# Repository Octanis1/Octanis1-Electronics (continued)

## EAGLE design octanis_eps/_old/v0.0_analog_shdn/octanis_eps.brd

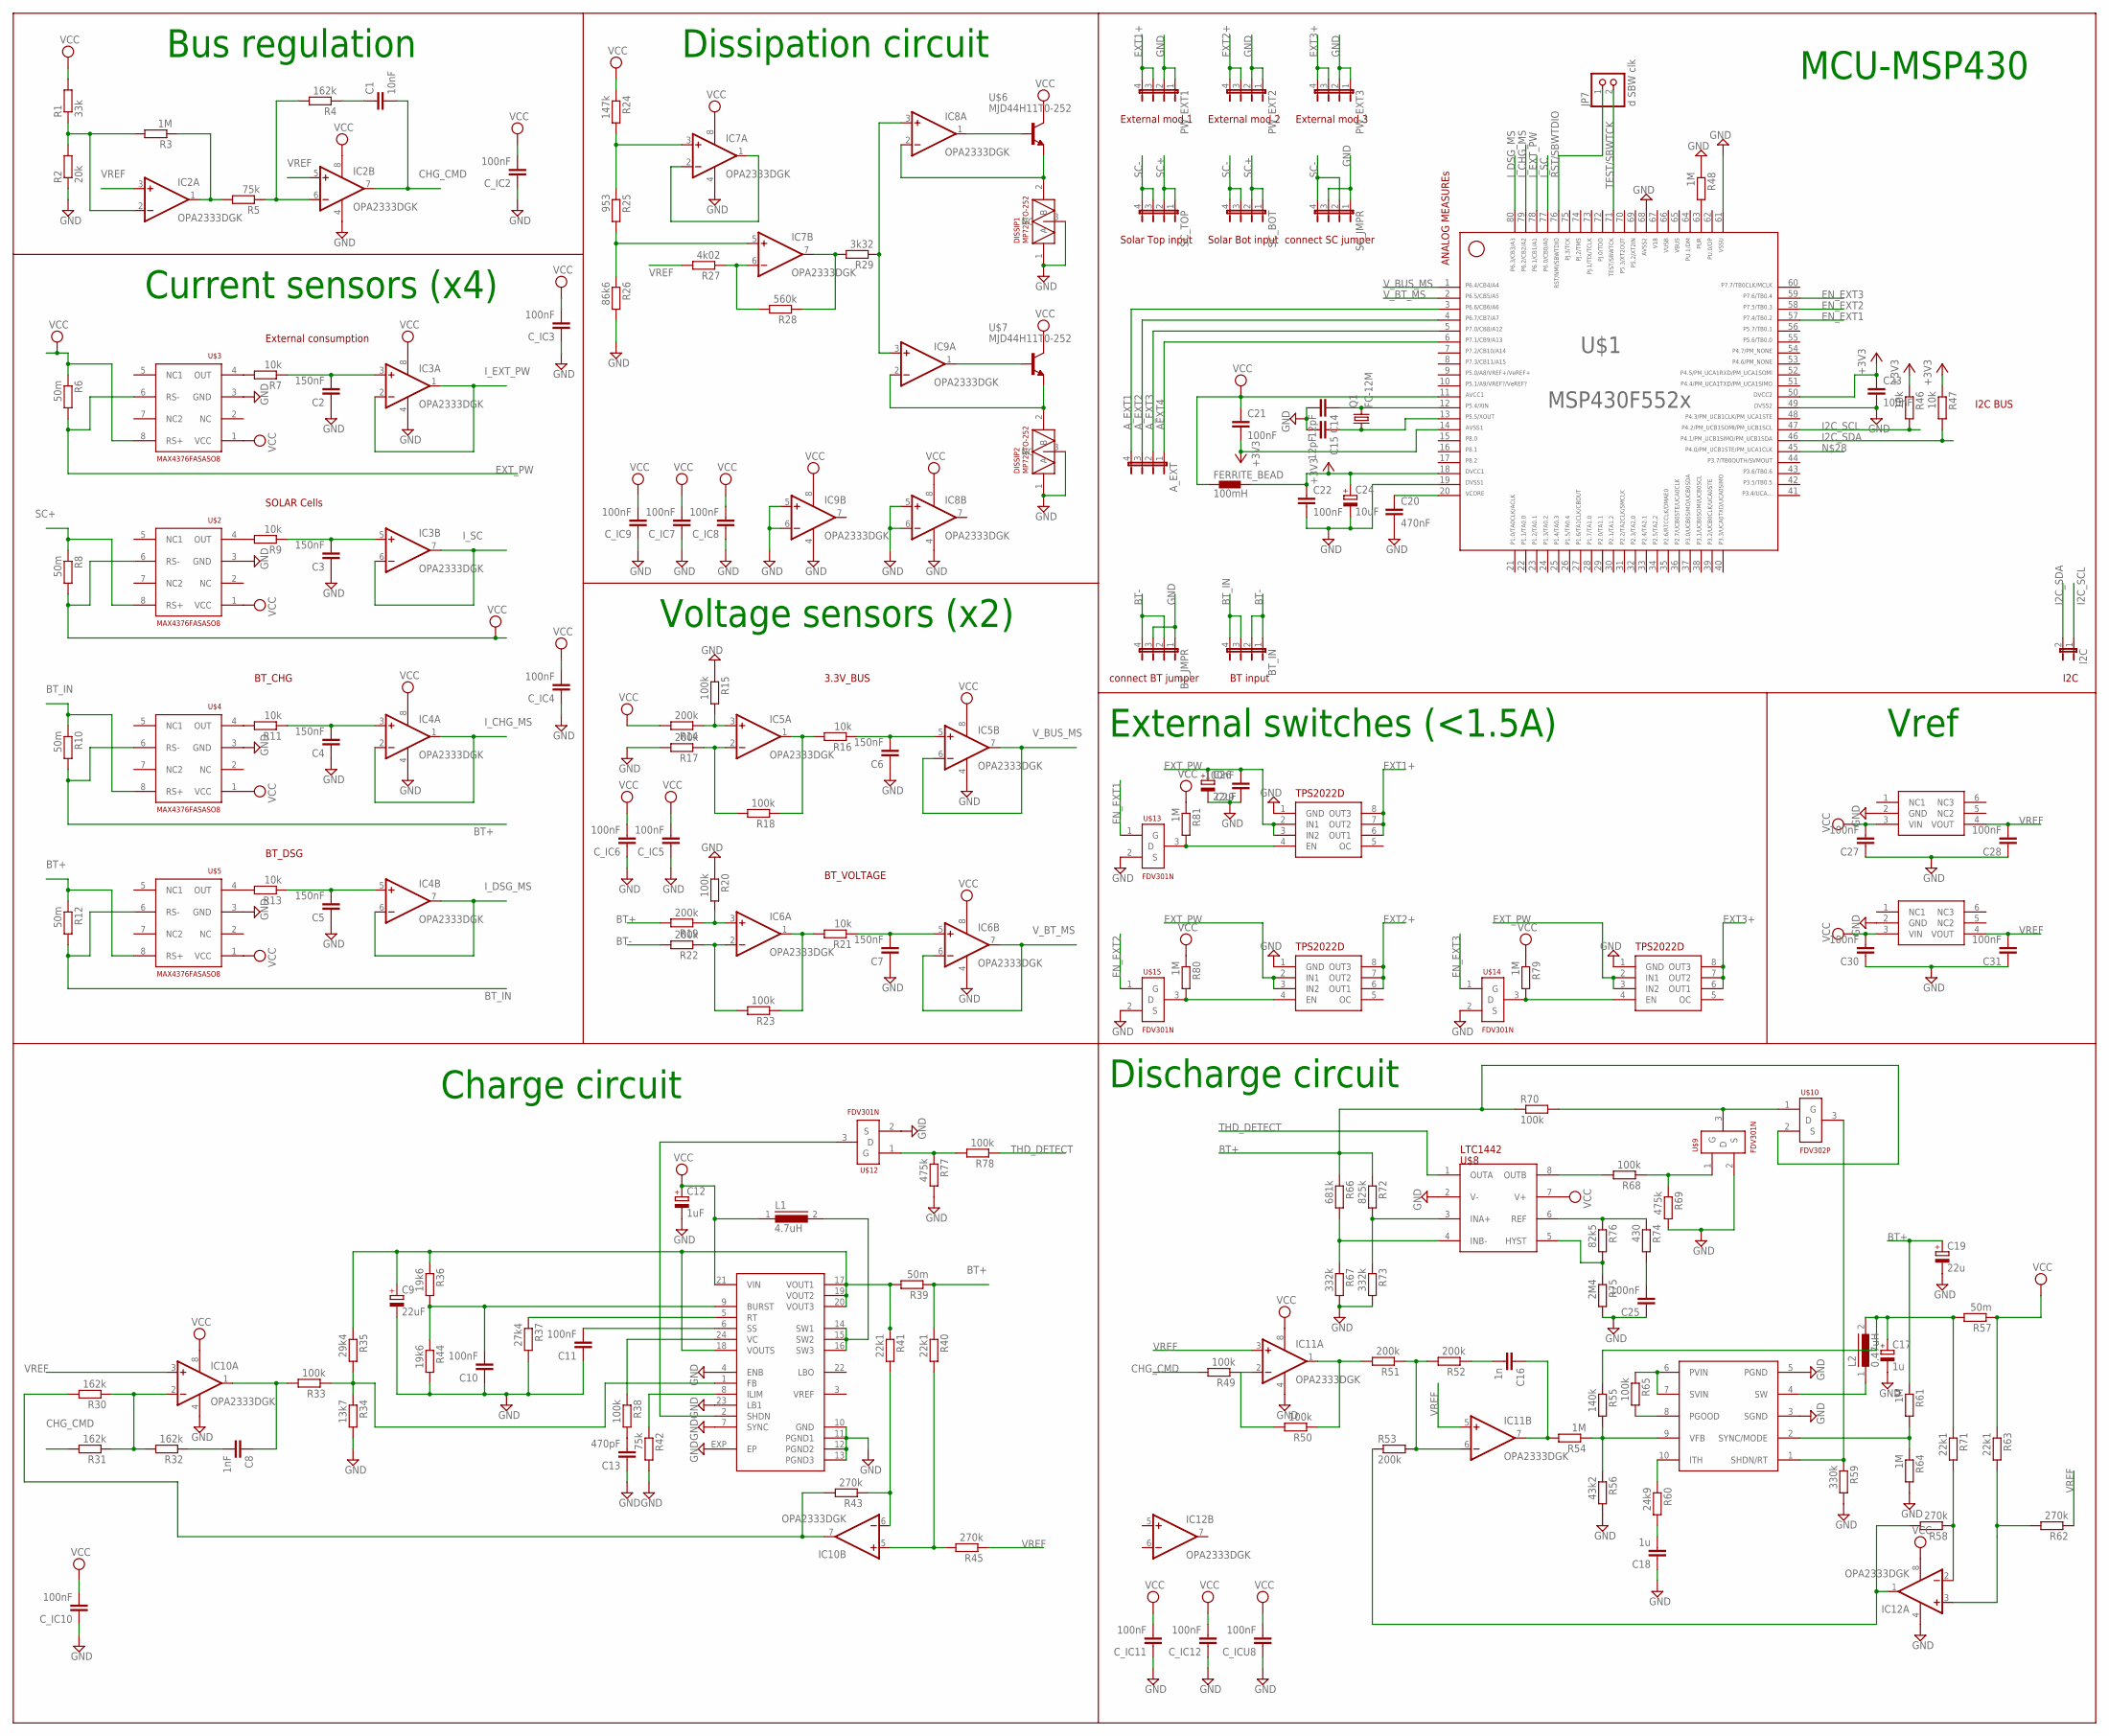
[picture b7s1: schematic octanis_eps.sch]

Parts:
A_EXT: JP4E; JP4
BT_IN: JP4E; JP4
BT_JMPR: JP4E; JP4
C1: 10nF; C0603
C2, C3, C4, C5, C6, C7: 150nF; C0603
C8: 1nF; C0603
C9, C26: 22uF; A/3216-18R
C10, C11, C21, C22, C23, C25, C27, C28, C29, C30, C31: 100nF; C0603
C12: 1uF; A/3216-18R
C13: 470pF; C0603
C14, C15: 12pF; C0603
C16: 1n; C0603
C17: 1u; A/3216-18R
C18: 1u; C0603
C19: 22u; A/3216-18R
C20: 470nF; C0603
C24: 10uF; A/3216-18R
C_IC2, C_IC3, C_IC4, C_IC5, C_IC6, C_IC7, C_IC8, C_IC9, C_IC10, C_IC11, C_IC12: 100nF; C0603
C_ICU8: 100nF; C0603
DISSIP1, DISSIP2: MP725TO-252; TO252
FERRITE_BEAD: 100mH; 0402
I2C: JP1E; JP1
IC2, IC3, IC4, IC5, IC6, IC7, IC8, IC9, IC10, IC11, IC12: OPA2333DGK; MSOP08
JP7: d SBW clk; 1X02
L1: 4.7uH; DR73
L2: 0.47uH; DR73
LTC3411: LT3411; MSOP10
PW_EXT1, PW_EXT2, PW_EXT3: JP4E; JP4
Q1: FC-12M
R1: 33k; R0603
R2: 20k; R0603
R3, R48, R54, R61, R64, R79, R80, R81: 1M; R0603
R4, R30, R31, R32: 162k; R0603
R5, R42: 75k; R0603
R6, R8, R10, R12, R39, R57: 50m; R1206
R7, R9, R11, R13, R16, R21, R46, R47: 10k; R0603
R14, R17, R19, R22, R51, R52, R53: 200k; R0603
R15, R18, R20, R23, R33, R38, R49, R50, R65, R68, R70, R78: 100k; R0603
R24: 147k; R0603
R25: 953; R0603
R26: 86k6; R0603
R27: 4k02; R0603
R28: 560k; R0603
R29: 3k32; R0603
R34: 13k7; R0603
R35: 29k4; R0603
R36, R44: 19k6; R0603
R37: 27k4; R0603
R40, R41, R63, R71: 22k1; R0603
R43, R45, R58, R62: 270k; R0603
R55: 140k; R0603
R56: 43k2; R0603
R59: 330k; R0603
R60: 24k9; R0603
R66: 681k; R0603
R67, R73: 332k; R0603
R69, R77: 475k; R0603
R72: 825k; R0603
R74: 430; R0603
R75: 2M4; R0603
R76: 82k5; R0603
SC_BOT: JP4E; JP4
SC_JMPR: JP4E; JP4
SC_TOP: JP4E; JP4
U$1: F552X---PN80; PN80
U$2, U$3, U$4, U$5: MAX4376FASASO8; SO8
U$6, U$7: MJD44H11T0-252; TO252
U$8: LTC1442; SO8
U$9, U$12, U$13, U$14, U$15: FDV301N; SOT23
U$10: FDV302P; SOT23
U$11: LTC3421; QFN24
U$16, U$17, U$18: TPS2022D; SO8
U$19, U$20: ADR127B; TSOT23-6

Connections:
65: U$1.65
66: U$1.66
67: U$1.67
+3V3: C21.2, C22.1, C23.1, C24.+, FERRITE_BEAD.2, R46.1, R47.1, U$1.14, U$1.18, U$1.50
AEXT4: A_EXT.1, U$1.6
A_EXT1: A_EXT.4, U$1.3
A_EXT2: A_EXT.3, U$1.4
A_EXT3: A_EXT.2, U$1.5
BT+: C19.+, R10.2, R12.1, R19.2, R39.1, R40.1, R61.1, R66.1, R70.1, R72.1, U$4.6 (RS-), U$5.8 (RS+), U$10.2 (S)
BT-: BT_IN.1, BT_IN.2, BT_JMPR.2, BT_JMPR.4, R22.2
BT_IN: BT_IN.3, BT_IN.4, R10.1, R12.2, U$4.8 (RS+), U$5.6 (RS-)
CHG_CMD: C1.2, IC2.7 (OUT), R31.2, R49.2
EN_EXT1: U$1.57, U$13.1 (G)
EN_EXT2: U$1.58, U$15.1 (G)
EN_EXT3: U$1.59, U$14.1 (G)
EXT1+: PW_EXT1.3, PW_EXT1.4, U$16.6 (OUT1), U$16.7 (OUT2), U$16.8 (OUT3)
EXT2+: PW_EXT2.3, PW_EXT2.4, U$17.6 (OUT1), U$17.7 (OUT2), U$17.8 (OUT3)
EXT3+: PW_EXT3.3, PW_EXT3.4, U$18.6 (OUT1), U$18.7 (OUT2), U$18.8 (OUT3)
EXT_PW: C26.+, C29.2, R6.2, U$3.6 (RS-), U$16.2 (IN1), U$16.3 (IN2), U$17.2 (IN1), U$17.3 (IN2), U$18.2 (IN1), U$18.3 (IN2)
GND: BT_JMPR.1, BT_JMPR.3, C2.1, C3.1, C4.1, C5.1, C6.1, C7.1, C9.-, C10.1, C11.1, C12.-, C13.1, C14.2, C15.2, C17.-, C18.1, C19.-, C20.2, C22.2, C23.2, C24.-, C25.1, C26.-, C27.1, C28.1, C29.1, C30.1, C31.1, C_IC2.1, C_IC3.1, C_IC4.1, C_IC5.1, C_IC6.1, C_IC7.1, C_IC8.1, C_IC9.1, C_IC10.1, C_IC11.1, C_IC12.1, C_ICU8.1, DISSIP1.1 (A), DISSIP1.3 (NC), DISSIP2.1 (A), DISSIP2.3 (NC), IC2.4 (V-), IC3.4 (V-), IC4.4 (V-), IC5.4 (V-), IC6.4 (V-), IC7.4 (V-), IC8.4 (V-), IC8.5 (+IN), IC8.6 (-IN), IC9.4 (V-), IC9.5 (+IN), IC9.6 (-IN), IC10.4 (V-), IC11.4 (V-), IC12.4 (V-), LTC3411.3 (SGND), LTC3411.5 (PGND), PW_EXT1.1, PW_EXT1.2, PW_EXT2.1, PW_EXT2.2, PW_EXT3.1, PW_EXT3.2, R2.1, R15.1, R17.2, R20.1, R26.2, R34.2, R37.2, R42.2, R44.2, R48.1, R56.2, R59.2, R64.2, R67.2, R69.2, R73.2, R75.2, R77.2, SC_JMPR.1, SC_JMPR.3, U$1.19, U$1.49, U$1.61, U$1.68, U$2.3 (GND), U$3.3 (GND), U$4.3 (GND), U$5.3 (GND), U$8.2 (V-), U$9.2 (S), U$11.4 (ENB), U$11.7 (SYNC), U$11.10 (GND), U$11.11 (PGND1), U$11.12 (PGND2), U$11.13 (PGND3), U$11.23 (LB1), U$11.EXP (EP), U$12.2 (S), U$13.2 (S), U$14.2 (S), U$15.2 (S), U$16.1 (GND), U$17.1 (GND), U$18.1 (GND), U$19.2 (GND), U$20.2 (GND)
I2C_SCL: I2C.1, R46.2, U$1.47
I2C_SDA: I2C.2, R47.2, U$1.46
I_CHG_MS: IC4.1 (OUT), IC4.2 (-IN), U$1.79
I_DSG_MS: IC4.6 (-IN), IC4.7 (OUT), U$1.80
I_EXT_PW: IC3.1 (OUT), IC3.2 (-IN), U$1.78
I_SC: IC3.6 (-IN), IC3.7 (OUT), U$1.77
unnamed: IC2.2 (-IN), R1.1, R2.2, R3.2
unnamed: IC2.1 (OUT), R3.1, R5.2
unnamed: C1.1, R4.1
unnamed: IC2.6 (-IN), R4.2, R5.1
unnamed: C4.2, IC4.3 (+IN), R11.1
unnamed: C2.2, IC3.3 (+IN), R7.1
unnamed: C3.2, IC3.5 (+IN), R9.1
unnamed: C5.2, IC4.5 (+IN), R13.1
unnamed: C7.2, IC6.5 (+IN), R21.1
unnamed: IC6.1 (OUT), R21.2, R23.1
unnamed: C6.2, IC5.5 (+IN), R16.1
unnamed: IC5.1 (OUT), R16.2, R18.1
unnamed: IC5.2 (-IN), R17.1, R18.2
unnamed: IC5.3 (+IN), R14.1, R15.2
unnamed: IC6.2 (-IN), R22.1, R23.2
unnamed: IC6.3 (+IN), R19.1, R20.2
unnamed: IC7.1 (OUT), IC7.2 (-IN)
unnamed: IC7.3 (+IN), R24.2, R25.1
unnamed: IC7.5 (+IN), R25.2, R26.1
unnamed: IC7.6 (-IN), R27.1, R28.2
unnamed: IC7.7 (OUT), R28.1, R29.2
unnamed: IC8.3 (+IN), IC9.3 (+IN), R29.1
unnamed: IC10.2 (-IN), R30.1, R31.1, R32.2
unnamed: C8.2, R32.1
unnamed: C8.1, IC10.1 (OUT), R33.2
unnamed: R33.1, R34.1, R35.2, U$11.1 (FB)
unnamed: R48.2, U$1.63
unnamed: R42.1, U$11.8 (ILIM)
unnamed: C10.2, R36.2, R44.1, U$11.9 (BURST)
unnamed: C13.2, R38.2
unnamed: R37.1, U$11.5 (RT)
unnamed: C11.2, U$11.6 (SS)
unnamed: R80.2, U$15.3 (D), U$17.4 (EN)
unnamed: C18.2, R60.2
unnamed: R38.1, U$11.24 (VC)
unnamed: U$11.2 (SHDN), U$12.3 (D)
unnamed: IC10.5 (+IN), R40.2, R45.2
unnamed: IC10.6 (-IN), R41.2, R43.1
unnamed: R9.2, U$2.4 (OUT)
unnamed: R11.2, U$4.4 (OUT)
unnamed: R7.2, U$3.4 (OUT)
unnamed: R13.2, U$5.4 (OUT)
unnamed: IC8.1 (OUT), U$6.1 (B)
unnamed: IC9.1 (OUT), U$7.1 (B)
unnamed: DISSIP2.2 (B), IC9.2 (-IN), U$7.3 (E)
unnamed: DISSIP1.2 (B), IC8.2 (-IN), U$6.3 (E)
unnamed: C14.1, Q1.2, U$1.12
unnamed: C20.1, U$1.20
unnamed: C15.1, Q1.1, U$1.13
unnamed: C16.1, IC11.7 (OUT), R54.2
unnamed: IC11.2 (-IN), R49.1, R50.2
unnamed: IC11.1 (OUT), R50.1, R51.2
unnamed: IC11.6 (-IN), R51.1, R52.2, R53.2
unnamed: C16.2, R52.1
unnamed: IC12.1 (OUT), R53.1, R58.2
unnamed: LTC3411.9 (VFB), R54.1, R55.2, R56.1
unnamed: C17.+, L2.2, R55.1, R57.2, R71.1
unnamed: LTC3411.10 (ITH), R60.1
unnamed: LTC3411.2 (SYNC/MODE), R61.2, R64.1
unnamed: IC12.2 (-IN), R58.1, R71.2
unnamed: IC12.3 (+IN), R62.2, R63.2
unnamed: LTC3411.8 (PGOOD), R65.2
unnamed: LTC3411.6 (PVIN), LTC3411.7 (SVIN), R65.1
unnamed: LTC3411.1 (SHDN/RT), R59.1, U$10.3 (D)
unnamed: R66.2, R67.1, U$8.4 (INB-)
unnamed: R68.2, U$8.8 (OUTB)
unnamed: R68.1, R69.1, U$9.1 (G)
unnamed: R72.2, R73.1, U$8.3 (INA+)
unnamed: R70.2, U$9.3 (D), U$10.1 (G)
unnamed: R74.1, R76.1, U$8.6 (REF)
unnamed: R75.1, R76.2, U$8.5 (HYST)
unnamed: C25.2, R74.2
unnamed: C9.+, R35.1, R36.1, R39.2, R41.1, U$11.17 (VOUT1), U$11.18 (VOUTS), U$11.19 (VOUT2), U$11.20 (VOUT3)
unnamed: R77.1, R78.2, U$12.1 (G)
unnamed: L2.1, LTC3411.4 (SW)
unnamed: L1.2, U$11.14 (SW1), U$11.15 (SW2), U$11.16 (SW3)
unnamed: R81.2, U$13.3 (D), U$16.4 (EN)
unnamed: R79.2, U$14.3 (D), U$18.4 (EN)
RST/SBWTDIO: JP7.1, U$1.76
SC+: R8.1, SC_BOT.1, SC_BOT.2, SC_TOP.1, SC_TOP.2, U$2.8 (RS+)
SC-: SC_BOT.3, SC_BOT.4, SC_JMPR.2, SC_JMPR.4, SC_TOP.3, SC_TOP.4
TEST/SBWTCK: JP7.2, U$1.71
THD_DETECT: R78.1, U$8.1 (OUTA)
UUU: IC10.7 (OUT), R30.2, R43.2
VCC: C12.+, C21.1, C27.2, C30.2, C_IC2.2, C_IC3.2, C_IC4.2, C_IC5.2, C_IC6.2, C_IC7.2, C_IC8.2, C_IC9.2, C_IC10.2, C_IC11.2, C_IC12.2, C_ICU8.2, FERRITE_BEAD.1, IC2.8 (V+), IC3.8 (V+), IC4.8 (V+), IC5.8 (V+), IC6.8 (V+), IC7.8 (V+), IC8.8 (V+), IC9.8 (V+), IC10.8 (V+), IC11.8 (V+), IC12.8 (V+), L1.1, R1.2, R6.1, R8.2, R14.2, R24.1, R57.1, R63.1, R79.1, R80.1, R81.1, U$1.11, U$2.1 (VCC), U$2.6 (RS-), U$3.1 (VCC), U$3.8 (RS+), U$4.1 (VCC), U$5.1 (VCC), U$6.2 (C), U$7.2 (C), U$8.7 (V+), U$11.21 (VIN), U$19.3 (VIN), U$20.3 (VIN)
VREF: C28.2, C31.2, IC2.3 (+IN), IC2.5 (+IN), IC10.3 (+IN), IC11.3 (+IN), IC11.5 (+IN), R27.2, R45.1, R62.1, U$19.4 (VOUT), U$20.4 (VOUT)
V_BT_MS: IC6.6 (-IN), IC6.7 (OUT), U$1.2
V_BUS_MS: IC5.6 (-IN), IC5.7 (OUT), U$1.1

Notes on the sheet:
Bus regulation
Vref
Current sensors (x4)
SOLAR Cells
3.3V_BUS
Charge circuit
Discharge circuit
External switches (<1.5A)
MCU-MSP430
BT_CHG
BT_DSG
Voltage sensors (x2)
BT_VOLTAGE
Dissipation circuit
I2C BUS
ANALOG MEASUREs
connect BT jumper
BT input
Solar Bot input
Solar Top input
External mod 2
External mod 1
I2C
External mod 3
External consumption
connect SC jumper

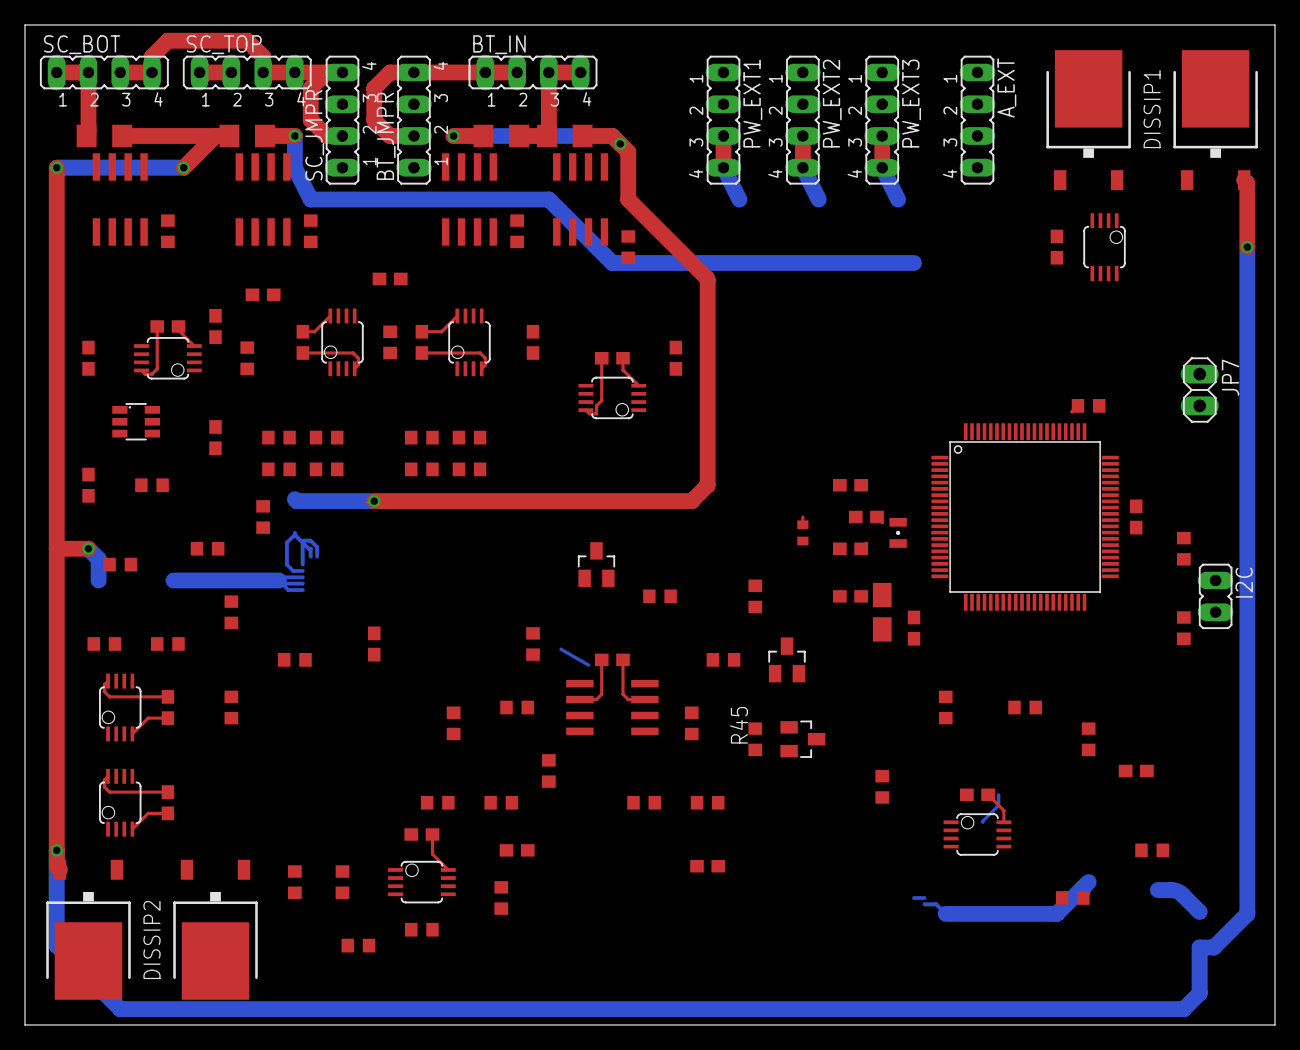
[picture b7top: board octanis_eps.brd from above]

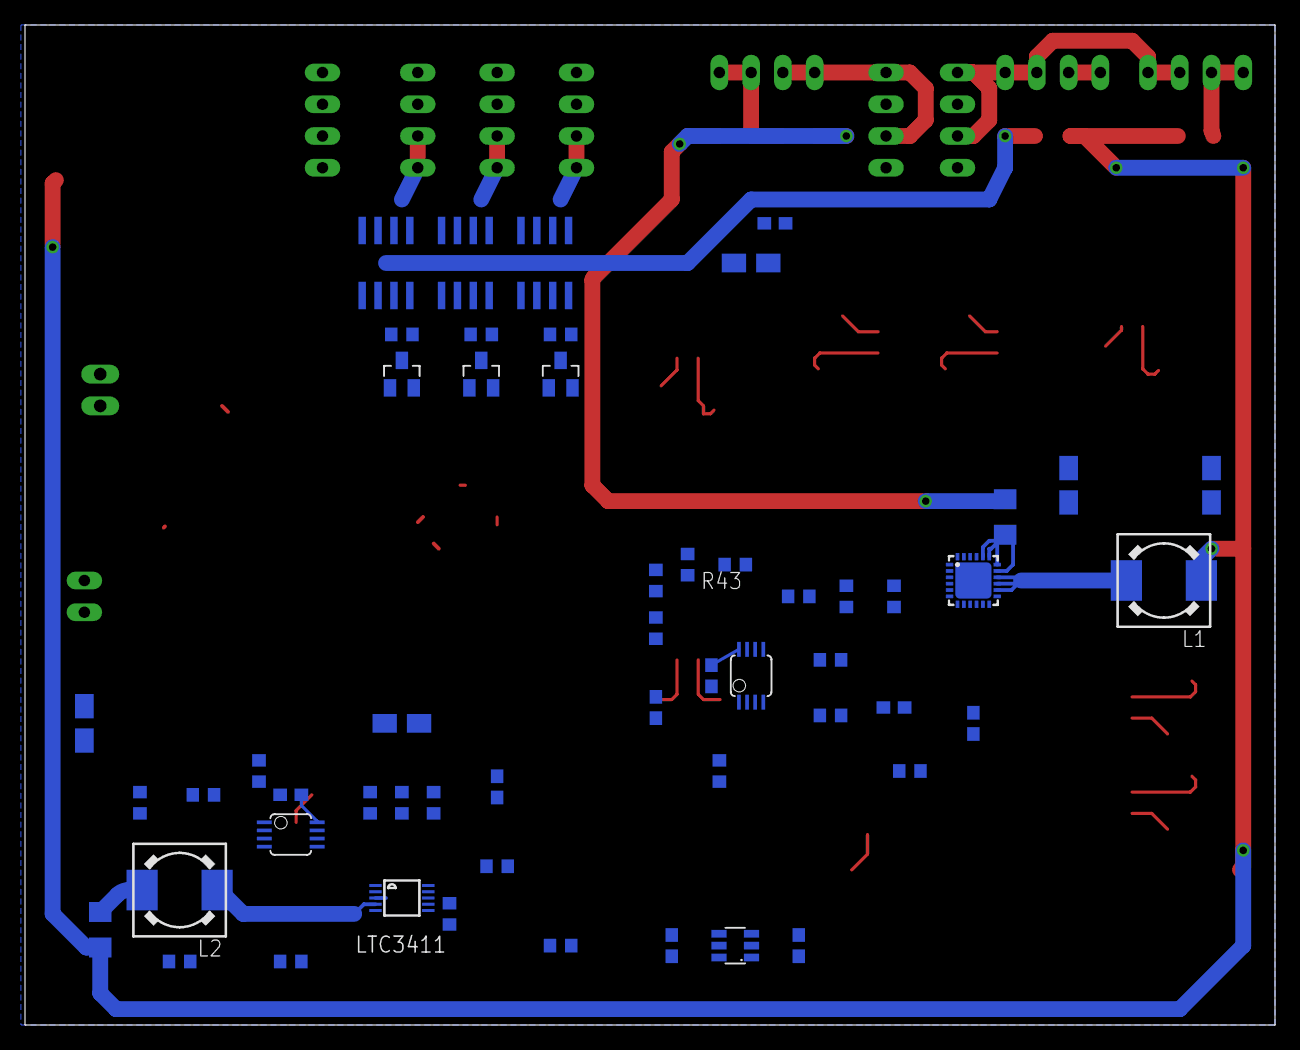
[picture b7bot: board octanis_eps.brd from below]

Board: 2 copper layers, 100.0 x 80.0 mm, 173 parts (54 on the bottom side), 111 nets.
